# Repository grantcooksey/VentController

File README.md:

# VentController

Cheap automatic humidity control for bathroom vents.

# TODO
* Firmware
* Blog post
* Packaging
* BOM (maybe)

View this project on [CADLAB.io](https://cadlab.io/project/26403).

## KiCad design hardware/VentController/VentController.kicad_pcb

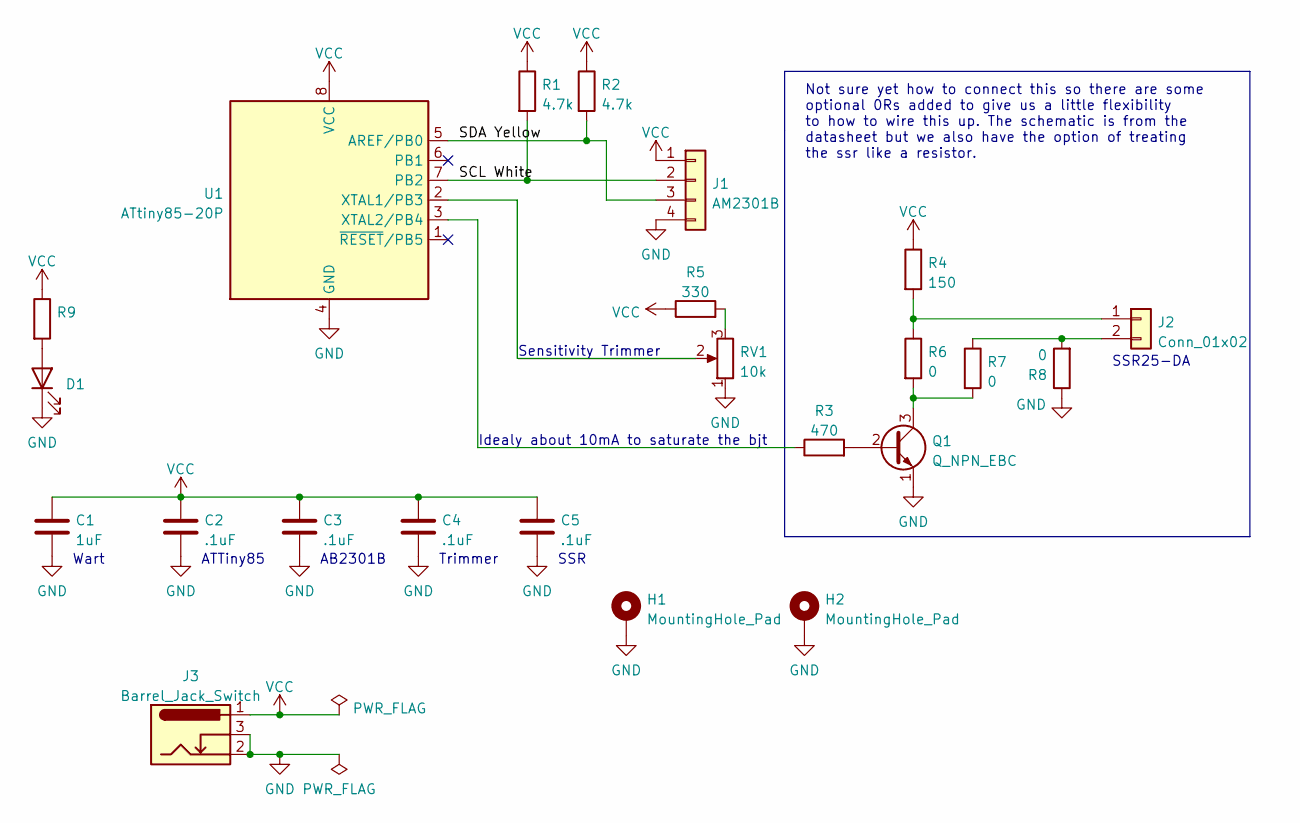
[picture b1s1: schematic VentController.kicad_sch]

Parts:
C1: 1uF; C_0805_2012Metric_Pad1.18x1.45mm_HandSolder
C2, C3, C4, C5: .1uF; C_0805_2012Metric_Pad1.18x1.45mm_HandSolder
D1: (no value)
H1, H2: MountingHole_Pad; MountingHole_2.5mm_Pad
J1: AM2301B; PinHeader_1x04_P2.54mm_Vertical
J2: Conn_01x02; PinHeader_1x02_P2.54mm_Vertical
J3: Barrel_Jack_Switch; BarrelJack_Horizontal
Q1: Q_NPN_EBC; TO-92_Inline
R1, R2: 4.7k; R_0805_2012Metric_Pad1.20x1.40mm_HandSolder
R3: 470; R_0805_2012Metric_Pad1.20x1.40mm_HandSolder
R4: 150; R_0805_2012Metric_Pad1.20x1.40mm_HandSolder
R5: 330; R_0805_2012Metric_Pad1.20x1.40mm_HandSolder
R6, R7, R8: 0; R_0805_2012Metric_Pad1.20x1.40mm_HandSolder
R9: (no value)
RV1: 10k; PinHeader_1x03_P2.54mm_Vertical
U1: ATtiny85-20P; DIP-8_W7.62mm

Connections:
/SCL White: J1.2, R1.2, U1.7 (PB2)
/SDA Yellow: J1.3, R2.2, U1.5 (AREF/PB0)
GND: C1.2, C2.2, C3.2, C4.2, C5.2, D1.1 (K), H1.1, H2.1, J1.4, J3.2, J3.3, Q1.1 (E), R8.1, RV1.1, U1.4 (GND)
unnamed: D1.2 (A), R9.2
unnamed: J2.1, R4.2, R6.1
unnamed: J2.2, R7.1, R8.2
unnamed: Q1.2 (B), R3.2
unnamed: Q1.3 (C), R6.2, R7.2
unnamed: R3.1, U1.3 (XTAL2/PB4)
unnamed: R5.2, RV1.3
unnamed: RV1.2, U1.2 (XTAL1/PB3)
VCC: C1.1, C2.1, C3.1, C4.1, C5.1, J1.1, J3.1, R1.1, R2.1, R4.1, R5.1, R9.1, U1.8 (VCC)

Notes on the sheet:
Trimmer
Sensitivity Trimmer
SSR25-DA
Idealy about 10mA to saturate the bjt
Not sure yet how to connect this so there are some optional 0Rs added to give us a little flexibility to how to wire this up. The schematic is from the datasheet but we also have the option of treating the ssr like a resistor.
Wart
SSR
ATTiny85
AB2301B

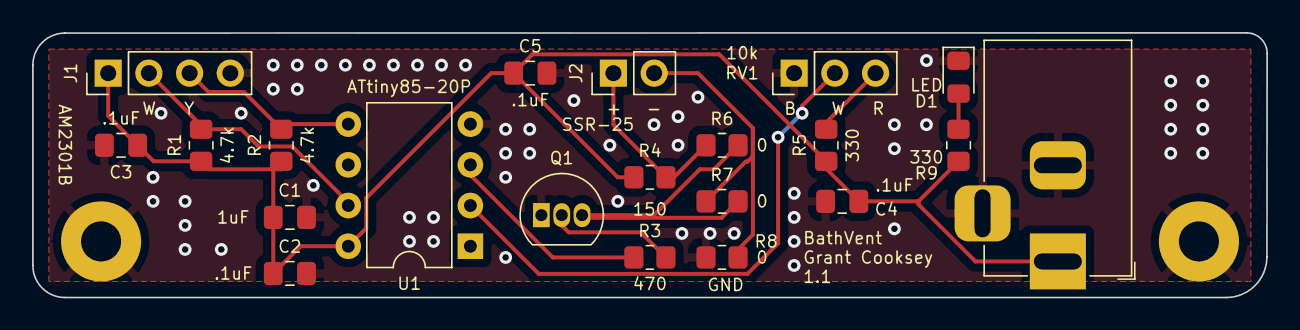
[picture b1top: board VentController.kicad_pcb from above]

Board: 2 copper layers, 77.0 x 16.5 mm, 23 parts (0 on the bottom side), 12 nets.

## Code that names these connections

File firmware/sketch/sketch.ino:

#include "AHT20.h"

#define PIN_SDA PB0
#define PIN_SCL PB2
#define PIN_ANALOG_HUMIDITY_SHUTOFF_LEVEL PB3
#define PIN_MOTOR_RELAY PB4

// 0-1023 (10 bit ADC) on ATTinys
#define ADC_MAX_RANGE 1023
#define ONE_SECOND 1000

AHT20 AHT;

void setup() {
    pinMode(PIN_MOTOR_RELAY, OUTPUT);
    pinMode(PIN_ANALOG_HUMIDITY_SHUTOFF_LEVEL, INPUT);
    setupHumiditySensor();
}

void loop() {
    int humidityShutoffLevel = readHumidityShutoffLevel();
    int currentHumidityLevel = readCurrentHumidityLevel();
    if (currentHumidityLevel < humidityShutoffLevel) {
        enableFan();
    } else {
        disableFan();
    }
    delay(ONE_SECOND);
}

void setupHumiditySensor() {
    delay(100);
    AHT.begin();
    delay(100);
}

void enableFan() {
    digitalWrite(PIN_MOTOR_RELAY, HIGH);
}

void disableFan() {
    digitalWrite(PIN_MOTOR_RELAY, LOW);
}

int readCurrentHumidityLevel() {
    float humidity;
    float temp;

    // should we add an error indicator?
    AHT.getSensor(&humidity, &temp);
    humidity *= ADC_MAX_RANGE;
    return (int)humidity;
}

int readHumidityShutoffLevel() {
    return analogRead(PIN_ANALOG_HUMIDITY_SHUTOFF_LEVEL);
}

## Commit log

2023-01-18 Backlink to CADLAB.io has been added.
2023-01-18 intial commit
2023-01-18 Add power plane to schematic
2023-01-20 Add controller layout
2023-01-20 Add ssr25 decoupling cap
2023-01-20 Some footprints
2023-01-21 Add optional configurations to ssr
2023-01-21 Add decoupling caps for ssr and trimmer
2023-01-21 Add power jack
2023-01-26 Set pcb board edges
2023-01-27 Lay out pcb
2023-01-27 Finishing touches
2023-01-27 Firmware template
2023-02-07 Better labels
2023-02-07 Feedback from board
    * Added power led
    * Updated text
    * Adjusted mounting hole layout
2023-02-07 Bump board version text
2023-02-07 Code skeleton
2023-02-08 Initial attempt at script
